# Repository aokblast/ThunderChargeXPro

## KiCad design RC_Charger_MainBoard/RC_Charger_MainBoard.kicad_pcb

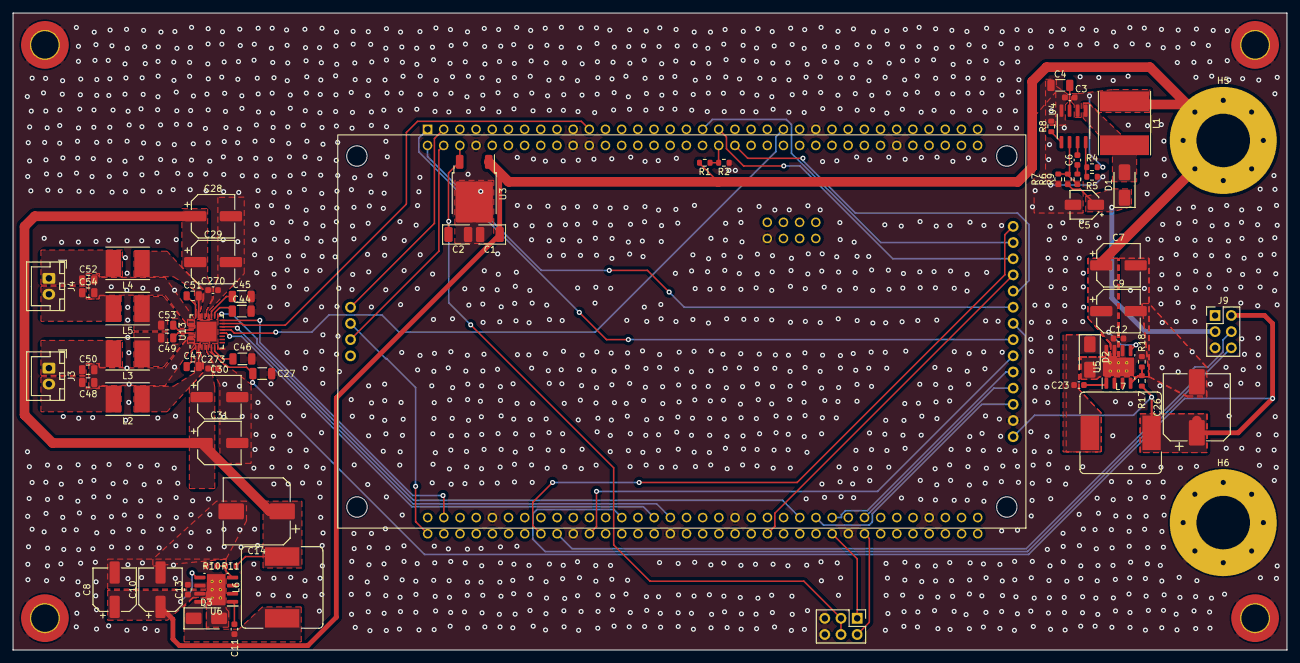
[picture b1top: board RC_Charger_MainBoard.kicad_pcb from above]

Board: 2 copper layers, 200.0 x 100.0 mm, 73 parts (1 on the bottom side), 59 nets.

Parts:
C1, C2: 10u; CP_EIA-3528-21_Kemet-B
C3, C11, C12, C13, C23, C270, C273: 0.1u; C_0603_1608Metric
C4, C27, C44, C45, C46: 1u; C_1206_3216Metric
C5: 10u; CP_Elec_4x5.7
C6: 2.2n; C_0603_1608Metric
C7, C8, C9, C10: 68u; CP_Elec_6.3x7.7
C14, C26: 560u; CP_Elec_10x10
C28, C29, C30, C31: 22u; CP_Elec_6.3x5.4
C47, C49, C51, C53: 0.47u; C_0805_2012Metric
C48, C50, C52, C54: 0.68u; C_0805_2012Metric
D1: CDBA360-HF; D_SMA
D2, D3: SS54F; D_SMA
H1, H2, H3, H4: M4; MountingHole_4.3mm_M4_DIN965_Pad_TopBottom
H5, H6: M8; MountingHole_8.4mm_M8_Pad_Via
J1, J9: Conn_02x03_Odd_Even; PinHeader_2x03_P2.54mm_Vertical
J3: SPK1; JST_XH_B2B-XH-A_1x02_P2.50mm_Vertical
J4: SPK2; JST_XH_B2B-XH-A_1x02_P2.50mm_Vertical
L1: 100u; L_Taiyo-Yuden_NR-80xx_HandSoldering
L2, L3, L4, L5: 10u; L_Taiyo-Yuden_NR-50xx_HandSoldering
L6, L7: 15u; L_Bourns_SRR1260
R1: 68k; R_0603_1608Metric
R2, R10, R17: 10k; R_0603_1608Metric
R4: 53.6k; R_0603_1608Metric
R5: 12.1k; R_0603_1608Metric
R6: 54.9k; R_0603_1608Metric
R7: 2.43k; R_0603_1608Metric
R8: 52.3k; R_0603_1608Metric
R9: 73.2k; R_0603_1608Metric
R11: 3.24k; R_0603_1608Metric
R18: 5.9k; R_0603_1608Metric
U1: NUCLEO-H745ZI-Q; MODULE_NUCLEO-H745ZI-Q
U2: 4-inch SPI screen
U3: L7805; TO-252-2
U4: LM5001MA; SOIC-8_3.9x4.9mm_P1.27mm
U5, U6: TPS5430DDA; Texas_R-PDSO-G8_EP2.95x4.9mm_Mask2.4x3.1mm_ThermalVias
U13: TAS5825MRHB; VQFN-32-1EP_5x5mm_P0.5mm_EP3.1x3.1mm

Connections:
+5V: C2.1, J1.3, J1.4, U1.CN11_6 (5V_EXT), U3.3 (OUT)
/3V3 Buck/FB: R17.1, R18.2, U5.4 (VSENSE)
/5V Buck/FB: R10.1, R11.2, U6.4 (VSENSE)
/5V Buck/VOUT: C14.1, C28.1, C29.1, C30.1, C31.1, C270.1, C273.1, L6.2, R10.2, U13.3 (PVDD), U13.4 (PVDD), U13.21 (PVDD), U13.22 (PVDD)
GND: C1.2, C2.2, C3.2, C4.2, C5.2, C7.2, C8.2, C9.2, C10.2, C12.2, C13.2, C14.2, C26.2, C27.2, C28.2, C29.2, C30.2, C31.2, C44.2, C45.2, C46.2, C48.2, C50.2, C52.2, C54.2, C270.2, C273.2, D2.2 (A), D3.2 (A), H1.1, H2.1, H3.1, H4.1, H6.1, J1.5, J1.6, J9.5, R2.2, R5.1, R7.1, R8.1, R11.1, R18.1, U1.CN6_7 (GND_CN6), U1.CN11_8 (GND), U1.CN11_19 (GND), U1.CN11_20 (GND), U1.CN11_22 (GND), U1.CN11_49 (GND), U1.CN11_60 (GND), U1.CN12_9 (GND), U1.CN12_20 (GND), U1.CN12_32 (AGND), U1.CN12_39 (GND), U1.CN12_54 (GND), U1.CN12_63 (GND), U2.2 (GND), U3.2 (GND), U4.4 (GND), U5.6 (GND), U5.9 (GNDPAD), U6.6 (GND), U6.9 (GNDPAD), U13.5 (DGND), U13.8 (ADR), U13.20 (AGND), U13.25 (PGND), U13.26 (PGND), U13.31 (PGND), U13.32 (PGND), U13.33 (EP)
I2S_CLK: U1.CN12_31 (PB3), U13.14 (SDIN)
I2S_LRCLK: U1.CN12_29 (PB5/PA4), U13.12 (LRCLK)
I2S_MUTE: U1.CN12_47 (PE10), U13.17 (~PDN)
I2S_SCL: U1.CN12_3 (PB8), U13.16 (SCL)
I2S_SDA: U1.CN11_21 (PB7), U13.15 (SDA)
I2S_SDO: U1.CN11_45 (PD7), U13.13 (SCLK)
IO_SCL: J9.6, U1.CN12_25 (PB10)
IO_SDA: J9.4, U1.CN12_18 (PB11)
unnamed: C6.2, R9.2
unnamed: D1.2 (A), L1.2, U4.1 (SW)
unnamed: C23.2, D2.1 (K), L7.1, U5.8 (PH)
unnamed: C11.2, D3.1 (K), L6.1, U6.8 (PH)
unnamed: C50.1, J3.1, L3.2
unnamed: C48.1, J3.2, L2.2
unnamed: C52.1, J4.1, L4.2
unnamed: C54.1, J4.2, L5.2
unnamed: C6.1, U4.7 (COMP)
unnamed: R4.1, R5.2, U4.8 (EN)
unnamed: R6.1, R7.2, R9.1, U4.6 (FB)
unnamed: R8.2, U4.5 (RT)
unnamed: C4.1, U4.3 (VCC)
unnamed: C23.1, U5.1 (BOOT)
unnamed: C11.1, U6.1 (BOOT)
unnamed: C45.1, U13.19 (AVDD)
unnamed: C47.1, U13.1 (BST_A+)
unnamed: C49.1, U13.29 (BST_A-)
unnamed: C51.1, U13.24 (BST_B+)
unnamed: C53.1, U13.28 (BST_B-)
unnamed: C44.1, U13.18 (GVDD)
unnamed: C47.2, L2.1, U13.2 (OUT_A+)
unnamed: C49.2, L3.1, U13.30 (OUT_A-)
unnamed: C51.2, L4.1, U13.23 (OUT_B+)
unnamed: C53.2, L5.1, U13.27 (OUT_B-)
unnamed: C46.1, U13.7 (VR_DIG)
SDMMC1_CK: U1.CN11_3 (PC12), U2.18 (SD_SCK)
SDMMC1_CMD: U1.CN11_4 (PD2), U2.16 (SD_MOSI)
SDMMC1_DO: U1.CN12_2 (PC8), U2.17 (SD_MISO)
SERVO1: J1.1, U1.CN12_52 (PE9)
SERVO2: J1.2, U1.CN12_56 (PE11)
SSPI_MISO: U1.CN11_2 (PC11), U2.9 (SDO(MISO))
SSPI_MOSI: U1.CN12_22 (PB2), U2.6 (SDI(MOSI))
SSPI_SCK: U1.CN11_1 (PC10), U2.7 (SCK)
S_CS: U1.CN12_49 (PE12), U2.3 (CS)
S_DCRS: U1.CN12_51 (PE14), U2.5 (DC/RS)
S_PWR: C26.1, C27.1, J9.2, L7.2, R17.2, U2.1 (VCC), U2.8 (LED), U13.6 (DVDD)
S_RST: U1.CN12_55 (PE13), U2.4 (RESET)
TSPI_MISO: U1.CN11_35 (PC2), U2.13 (T_DO)
TSPI_MOSI: U1.CN11_37 (PC3), U2.12 (T_DIN)
TSPI_SCK: U1.CN11_40 (PD3), U2.10 (T_CLK)
T_CS: U1.CN12_44 (PE7), U2.11 (T_CS)
T_IRQ: U1.CN12_16 (PB12), U2.14 (T_IRQ)
VCC: C5.1, D1.1 (K), J9.3, R6.2
VIN: C1.1, C3.1, C7.1, C8.1, C9.1, C10.1, C12.1, C13.1, H5.1, L1.1, R1.1, R4.2, U3.1 (IN), U4.2 (VIN), U5.5 (EN), U5.7 (VIN), U6.5 (EN), U6.7 (VIN)
VSENSE: R1.2, R2.1, U1.CN11_38 (PC0)

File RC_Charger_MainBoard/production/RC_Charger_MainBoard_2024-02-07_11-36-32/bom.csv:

Designator,Footprint,Quantity,Value,LCSC Part #
"C1, C2",CP_EIA-3528-21_Kemet-B,2,10u,
"C10, C7, C8, C9",CP_Elec_6.3x7.7,4,68u,
"C11, C12, C13, C23, C270, C273, C3",0603,7,0.1u,
"C14, C26",CP_Elec_10x10,2,560u,
"C27, C4, C44, C45, C46",1206,5,1u,
"C28, C29, C30, C31",CP_Elec_6.3x5.4,4,22u,
"C47, C49, C51, C53",0805,4,0.47u,
"C48, C50, C52, C54",0805,4,0.68u,
C5,CP_Elec_4x5.7,1,10u,
C6,0603,1,2.2n,
D1,D_SMA,1,CDBA360-HF,
"D2, D3",D_SMA,2,SS54F,
"H1, H2, H3, H4",MountingHole_4.3mm_M4_DIN965_Pad_TopBottom,4,M4,
"H5, H6",MountingHole_8.4mm_M8_Pad_Via,2,M8,
"J1, J9",PinHeader_2x03_P2.54mm_Vertical,2,Conn_02x03_Odd_Even,
J3,JST_XH_B2B-XH-A_1x02_P2.50mm_Vertical,1,SPK1,
J4,JST_XH_B2B-XH-A_1x02_P2.50mm_Vertical,1,SPK2,
L1,L_Taiyo-Yuden_NR-80xx_HandSoldering,1,100u,
"L2, L3, L4, L5",L_Taiyo-Yuden_NR-50xx_HandSoldering,4,10u,
"L6, L7",L_Bourns_SRR1260,2,15u,
R1,0603,1,68k,
"R10, R17, R2",0603,3,10k,
R11,0603,1,3.24k,
R18,0603,1,5.9k,
R4,0603,1,53.6k,
R5,0603,1,12.1k,
R6,0603,1,54.9k,
R7,0603,1,2.43k,
R8,0603,1,52.3k,
R9,0603,1,73.2k,
U1,MODULE_NUCLEO-H745ZI-Q,1,NUCLEO-H745ZI-Q,
U13,VQFN-32-1EP_5x5mm_P0.5mm_EP3.1x3.1mm,1,TAS5825MRHB,
U2,4-inch SPI screen,1,~,
U3,TO-252-2,1,L7805,
U4,SOIC-8_3.9x4.9mm_P1.27mm,1,LM5001MA,
"U5, U6",Texas_R-PDSO-G8_EP2.95x4.9mm_Mask2.4x3.1mm_ThermalVias,2,TPS5430DDA,

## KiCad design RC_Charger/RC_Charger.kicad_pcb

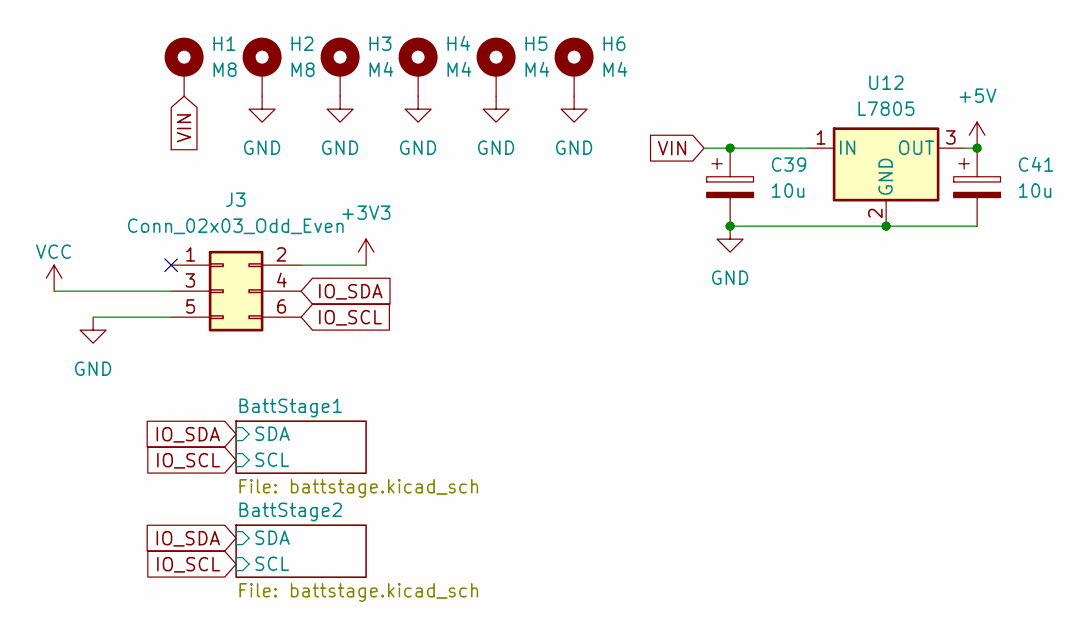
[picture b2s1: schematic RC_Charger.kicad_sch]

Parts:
C39, C41: 10u; CP_EIA-3528-21_Kemet-B
H1, H2: M8; MountingHole_8.4mm_M8_Pad_Via
H3, H4, H5, H6: M4; MountingHole_4.3mm_M4_DIN965_Pad_TopBottom
J3: Conn_02x03_Odd_Even; PinHeader_2x03_P2.54mm_Vertical
U12: L7805; TO-252-2

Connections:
+3V3: J3.2; also elsewhere on the board
+5V: C41.1, U12.3 (OUT); also elsewhere on the board
GND: C39.2, C41.2, H2.1, H3.1, H4.1, H5.1, H6.1, J3.5, U12.2 (GND); also elsewhere on the board
IO_SCL: J3.6; also elsewhere on the board
IO_SDA: J3.4; also elsewhere on the board
VCC: J3.3; also elsewhere on the board
VIN: C39.1, H1.1, U12.1 (IN); also elsewhere on the board

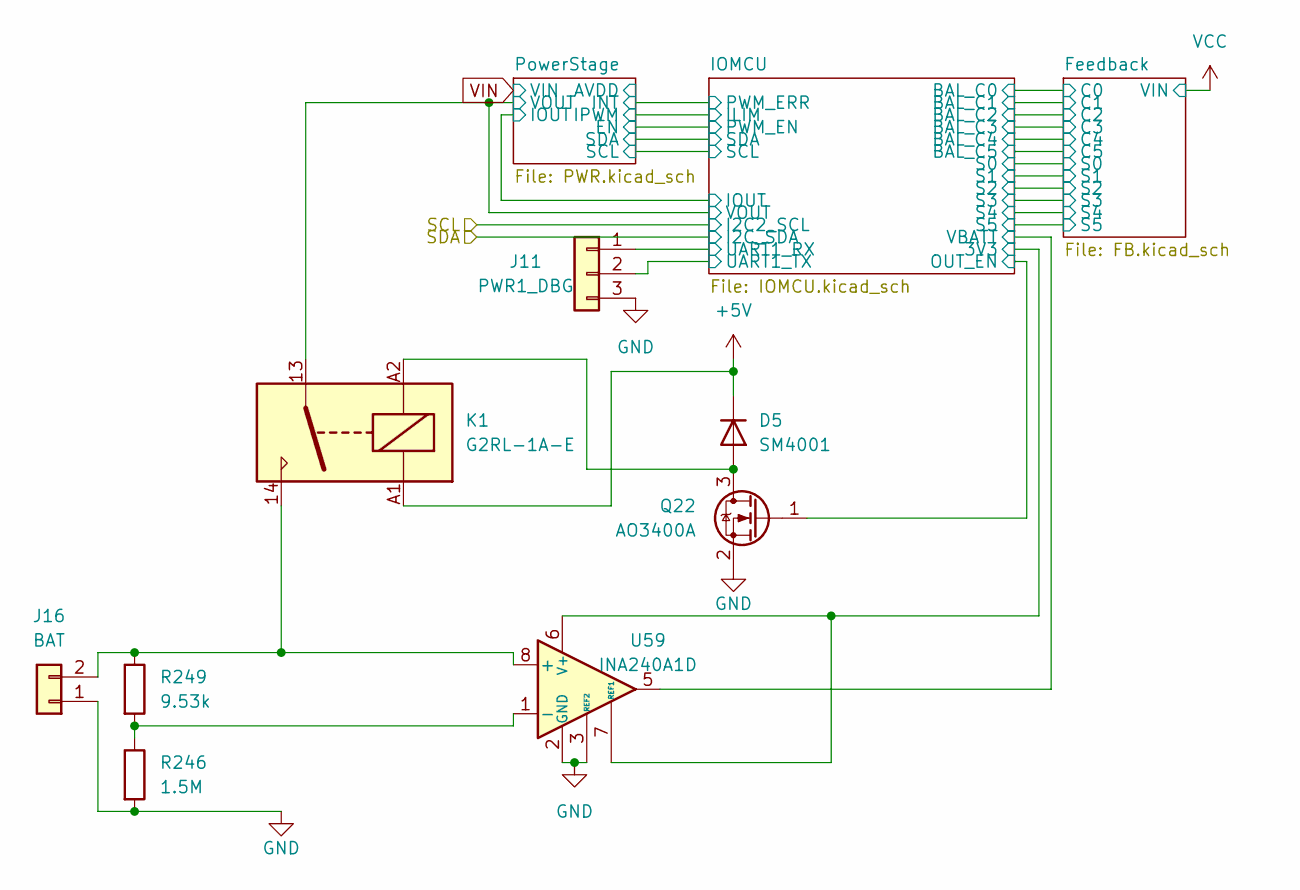
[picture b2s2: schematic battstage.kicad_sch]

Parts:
D5: SM4001; D_MELF
J11: PWR1_DBG; PinHeader_1x03_P2.54mm_Vertical
J16: BAT; TerminalBlock_Dinkle_DT-55-B01X-02_P10.00mm
K1: G2RL-1A-E; Relay_SPST_Omron_G2RL-1A-E
Q22: AO3400A; SOT-23
R246: 1.5M; R_0603_1608Metric
R249: 9.53k; R_0603_1608Metric
U59: INA240A1D; SOIC-8_3.9x4.9mm_P1.27mm

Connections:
+3V3: U59.6 (V+), U59.7 (REF1); also elsewhere on the board
+5V: D5.1 (K), K1.A1; also elsewhere on the board
/BattStage1/IOMCU/UART1_RX: J11.1; also elsewhere on the board
/BattStage1/IOMCU/UART1_TX: J11.2; also elsewhere on the board
/BattStage1/PowerStage/VOUT: K1.13; also elsewhere on the board
/BattStage2/IOMCU/OUT_EN: Q22.1 (G); also elsewhere on the board
/BattStage2/IOMCU/VBATT: U59.5; also elsewhere on the board
GND: J11.3, J16.1, Q22.2 (S), R246.2, U59.2 (GND), U59.3 (REF2), U59.4 (GND); also elsewhere on the board
unnamed: R246.1, R249.2, U59.1 (-)

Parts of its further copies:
D6: SM4001; D_MELF
J5: PWR1_DBG; PinHeader_1x03_P2.54mm_Vertical
J19: BAT; TerminalBlock_Dinkle_DT-55-B01X-02_P10.00mm
K2: G2RL-1A-E; Relay_SPST_Omron_G2RL-1A-E
Q21: AO3400A; SOT-23
R245: 1.5M; R_0603_1608Metric
R252: 9.53k; R_0603_1608Metric
U62: INA240A1D; SOIC-8_3.9x4.9mm_P1.27mm

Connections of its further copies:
+3V3: U62.6 (V+), U62.7 (REF1); also elsewhere on the board
+5V: D6.1 (K), K2.A1; also elsewhere on the board
/BattStage1/IOMCU/OUT_EN: Q21.1 (G); also elsewhere on the board
/BattStage1/IOMCU/VBATT: U62.5; also elsewhere on the board
/BattStage2/IOMCU/UART1_RX: J5.1; also elsewhere on the board
/BattStage2/IOMCU/UART1_TX: J5.2; also elsewhere on the board
/BattStage2/PowerStage/VOUT: K2.13; also elsewhere on the board
GND: J5.3, J19.1, Q21.2 (S), R245.2, U62.2 (GND), U62.3 (REF2), U62.4 (GND); also elsewhere on the board
unnamed: R245.1, R252.2, U62.1 (-)

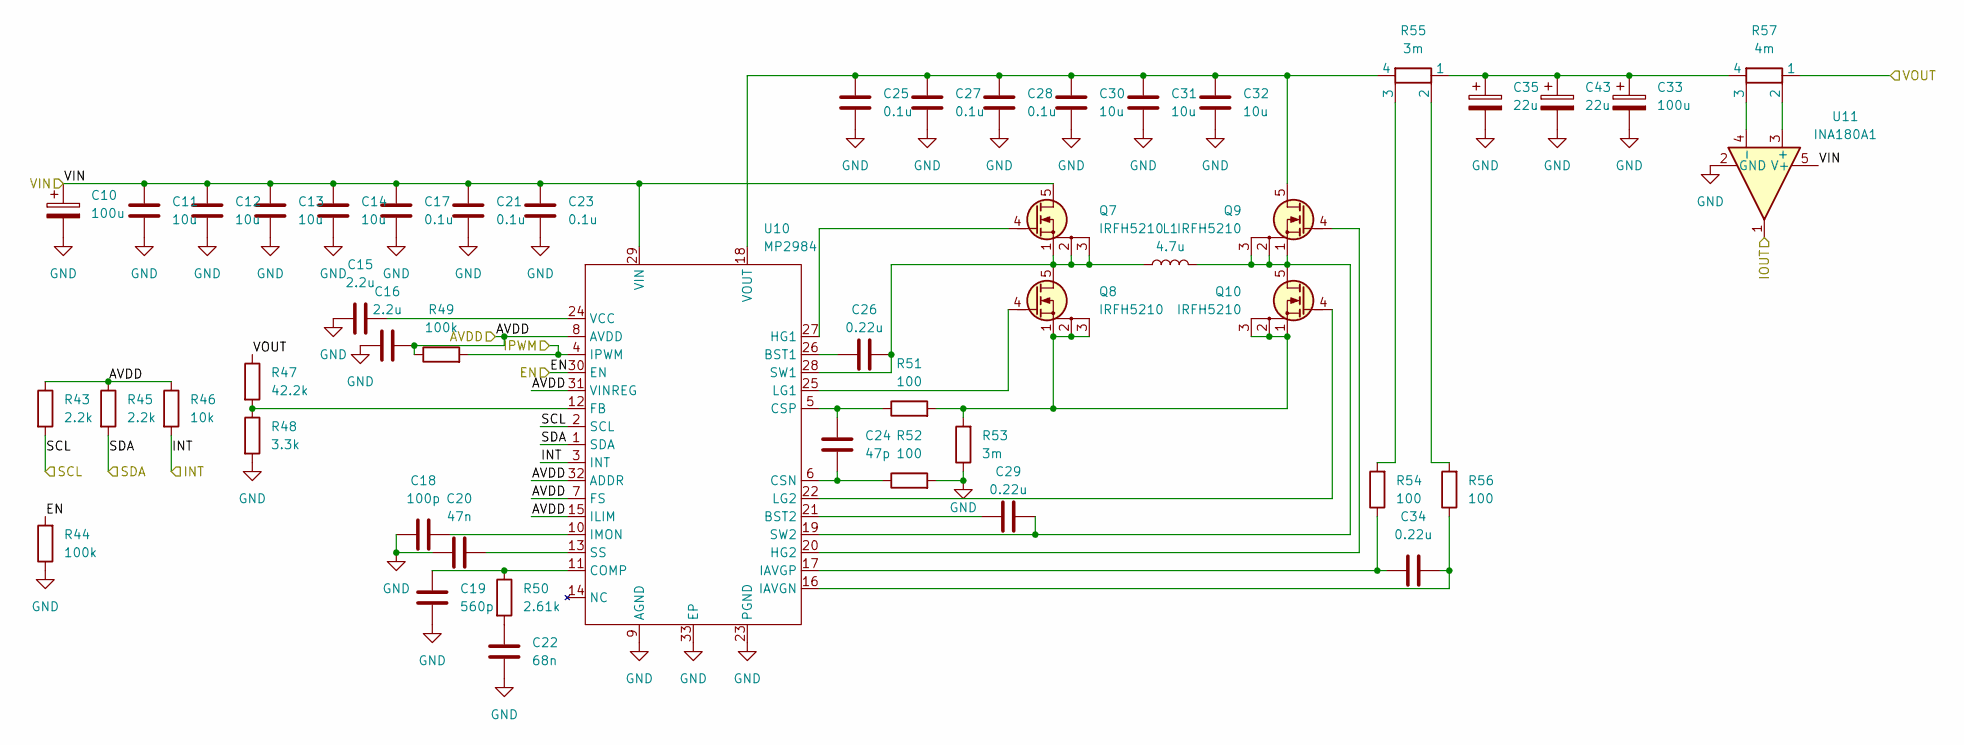
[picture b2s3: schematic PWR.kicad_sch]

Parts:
C10, C33: 100u; CP_Elec_6.3x7.7
C11, C12, C13, C14, C30, C31, C32: 10u; C_1206_3216Metric
C15, C16: 2.2u; C_0805_2012Metric
C17, C21, C23, C25, C27, C28: 0.1u; C_0603_1608Metric
C18: 100p; C_0603_1608Metric
C19: 560p; C_0603_1608Metric
C20: 47n; C_0603_1608Metric
C22: 68n; C_0603_1608Metric
C24: 47p; C_0603_1608Metric
C26, C29, C34: 0.22u; C_0603_1608Metric
C35, C43: 22u; CP_Elec_6.3x5.4
L1: 4.7u; L_Bourns_SRP1770TA_16.9x16.9mm
Q7, Q8, Q9, Q10: IRFH5210; PQFN-8-EP_6x5mm_P1.27mm_Generic
R43, R45: 2.2k; R_0603_1608Metric
R44, R49: 100k; R_0603_1608Metric
R46: 10k; R_0603_1608Metric
R47: 42.2k; R_0603_1608Metric
R48: 3.3k; R_0603_1608Metric
R50: 2.61k; R_0603_1608Metric
R51, R52, R54, R56: 100; R_0603_1608Metric
R53: 3m; R_Shunt_1575
R55: 3m; R_Shunt_Vishay_WSK2512_6332Metric_T2.21mm
R57: 4m; R_Shunt_Vishay_WSK2512_6332Metric_T2.21mm
U10: MP2984; QFN-32-1EP_4x4mm_P0.4mm_EP2.65x2.65mm
U11: INA180A1; SOT-23-5

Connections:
/BattStage1/IOMCU/ILIM: R49.2, U10.4 (IPWM); also elsewhere on the board
/BattStage1/IOMCU/IOUT: U11.1; also elsewhere on the board
/BattStage1/PowerStage/AVDD: C16.2, R43.1, R45.1, R46.1, R49.1, U10.7 (FS), U10.8 (AVDD), U10.15 (ILIM), U10.31 (VINREG), U10.32 (ADDR)
/BattStage1/PowerStage/EN: R44.2, U10.30 (EN); also elsewhere on the board
/BattStage1/PowerStage/INT: R46.2, U10.3 (INT); also elsewhere on the board
/BattStage1/PowerStage/SCL: R43.2, U10.2 (SCL); also elsewhere on the board
/BattStage1/PowerStage/SDA: R45.2, U10.1 (SDA); also elsewhere on the board
/BattStage1/PowerStage/VOUT: R47.1, R57.1; also elsewhere on the board
GND: C10.2, C11.2, C12.2, C13.2, C14.2, C15.1, C16.1, C17.2, C18.1, C19.2, C20.2, C21.2, C22.2, C23.2, C25.2, C27.2, C28.2, C30.2, C31.2, C32.2, C33.2, C35.2, C43.2, R44.1, R48.2, R52.2, R53.1, U10.9 (AGND), U10.23 (PGND), U10.33 (EP), U11.2 (GND); also elsewhere on the board
unnamed: C22.1, R50.2
unnamed: C33.1, C35.1, C43.1, R55.1, R57.4
unnamed: Q7.4 (G), U10.27 (HG1)
unnamed: C26.2, L1.1, Q7.1 (S), Q7.2 (S), Q7.3 (S), Q8.5 (D), U10.28 (SW1)
unnamed: Q8.4 (G), U10.25 (LG1)
unnamed: C25.1, C27.1, C28.1, C30.1, C31.1, C32.1, Q9.5 (D), R55.4, U10.18 (VOUT)
unnamed: Q9.4 (G), U10.20 (HG2)
unnamed: C29.2, L1.2, Q9.1 (S), Q9.2 (S), Q9.3 (S), Q10.5 (D), U10.19 (SW2)
unnamed: Q10.4 (G), U10.22 (LG2)
unnamed: Q8.1 (S), Q8.2 (S), Q8.3 (S), Q10.1 (S), Q10.2 (S), Q10.3 (S), R51.2, R53.2
unnamed: R54.2, R55.3
unnamed: R55.2, R56.2
unnamed: C26.1, U10.26 (BST1)
unnamed: C29.1, U10.21 (BST2)
unnamed: C19.1, R50.1, U10.11 (COMP)
unnamed: C24.2, R52.1, U10.6 (CSN)
unnamed: C24.1, R51.1, U10.5 (CSP)
unnamed: R47.2, R48.1, U10.12 (FB)
unnamed: C34.2, R56.1, U10.16 (IAVGN)
unnamed: C34.1, R54.1, U10.17 (IAVGP)
unnamed: C18.2, U10.10 (IMON)
unnamed: C20.1, U10.13 (SS)
unnamed: C15.2, U10.24 (VCC)
unnamed: R57.2, U11.3 (+)
unnamed: R57.3, U11.4 (-)
VIN: C10.1, C11.1, C12.1, C13.1, C14.1, C17.1, C21.1, C23.1, Q7.5 (D), U10.29 (VIN), U11.5 (V+); also elsewhere on the board

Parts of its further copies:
C36, C44: 22u; CP_Elec_6.3x5.4
C42, C55: 100u; CP_Elec_6.3x7.7
C56, C57, C58, C59, C75, C76, C77: 10u; C_1206_3216Metric
C60, C61: 2.2u; C_0805_2012Metric
C62, C66, C68, C70, C72, C73: 0.1u; C_0603_1608Metric
C63: 100p; C_0603_1608Metric
C64: 560p; C_0603_1608Metric
C65: 47n; C_0603_1608Metric
C67: 68n; C_0603_1608Metric
C69: 47p; C_0603_1608Metric
C71, C74, C79: 0.22u; C_0603_1608Metric
L6: 4.7u; L_Bourns_SRP1770TA_16.9x16.9mm
Q11, Q12, Q13, Q14: IRFH5210; PQFN-8-EP_6x5mm_P1.27mm_Generic
R62, R64: 2.2k; R_0603_1608Metric
R63, R68: 100k; R_0603_1608Metric
R65: 10k; R_0603_1608Metric
R66: 42.2k; R_0603_1608Metric
R67: 3.3k; R_0603_1608Metric
R69: 2.61k; R_0603_1608Metric
R70, R71, R73, R75: 100; R_0603_1608Metric
R72: 3m; R_Shunt_1575
R74: 3m; R_Shunt_Vishay_WSK2512_6332Metric_T2.21mm
R76: 4m; R_Shunt_Vishay_WSK2512_6332Metric_T2.21mm
U16: MP2984; QFN-32-1EP_4x4mm_P0.4mm_EP2.65x2.65mm
U17: INA180A1; SOT-23-5

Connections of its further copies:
/BattStage2/IOMCU/ILIM: R68.2, U16.4 (IPWM); also elsewhere on the board
/BattStage2/IOMCU/IOUT: U17.1; also elsewhere on the board
/BattStage2/PowerStage/AVDD: C61.2, R62.1, R64.1, R65.1, R68.1, U16.7 (FS), U16.8 (AVDD), U16.15 (ILIM), U16.31 (VINREG), U16.32 (ADDR)
/BattStage2/PowerStage/EN: R63.2, U16.30 (EN); also elsewhere on the board
/BattStage2/PowerStage/INT: R65.2, U16.3 (INT); also elsewhere on the board
/BattStage2/PowerStage/SCL: R62.2, U16.2 (SCL); also elsewhere on the board
/BattStage2/PowerStage/SDA: R64.2, U16.1 (SDA); also elsewhere on the board
/BattStage2/PowerStage/VOUT: R66.1, R76.1; also elsewhere on the board
GND: C36.2, C42.2, C44.2, C55.2, C56.2, C57.2, C58.2, C59.2, C60.1, C61.1, C62.2, C63.1, C64.2, C65.2, C66.2, C67.2, C68.2, C70.2, C72.2, C73.2, C75.2, C76.2, C77.2, R63.1, R67.2, R71.2, R72.1, U16.9 (AGND), U16.23 (PGND), U16.33 (EP), U17.2 (GND); also elsewhere on the board
unnamed: C36.1, C42.1, C44.1, R74.1, R76.4
unnamed: C67.1, R69.2
unnamed: Q11.4 (G), U16.27 (HG1)
unnamed: C71.2, L6.1, Q11.1 (S), Q11.2 (S), Q11.3 (S), Q12.5 (D), U16.28 (SW1)
unnamed: Q12.4 (G), U16.25 (LG1)
unnamed: Q12.1 (S), Q12.2 (S), Q12.3 (S), Q14.1 (S), Q14.2 (S), Q14.3 (S), R70.2, R72.2
unnamed: C70.1, C72.1, C73.1, C75.1, C76.1, C77.1, Q13.5 (D), R74.4, U16.18 (VOUT)
unnamed: Q13.4 (G), U16.20 (HG2)
unnamed: C74.2, L6.2, Q13.1 (S), Q13.2 (S), Q13.3 (S), Q14.5 (D), U16.19 (SW2)
unnamed: Q14.4 (G), U16.22 (LG2)
unnamed: R73.2, R74.3
unnamed: R74.2, R75.2
unnamed: C71.1, U16.26 (BST1)
unnamed: C74.1, U16.21 (BST2)
unnamed: C64.1, R69.1, U16.11 (COMP)
unnamed: C69.2, R71.1, U16.6 (CSN)
unnamed: C69.1, R70.1, U16.5 (CSP)
unnamed: R66.2, R67.1, U16.12 (FB)
unnamed: C79.2, R75.1, U16.16 (IAVGN)
unnamed: C79.1, R73.1, U16.17 (IAVGP)
unnamed: C63.2, U16.10 (IMON)
unnamed: C65.1, U16.13 (SS)
unnamed: C60.2, U16.24 (VCC)
unnamed: R76.2, U17.3 (+)
unnamed: R76.3, U17.4 (-)
VIN: C55.1, C56.1, C57.1, C58.1, C59.1, C62.1, C66.1, C68.1, Q11.5 (D), U16.29 (VIN), U17.5 (V+); also elsewhere on the board

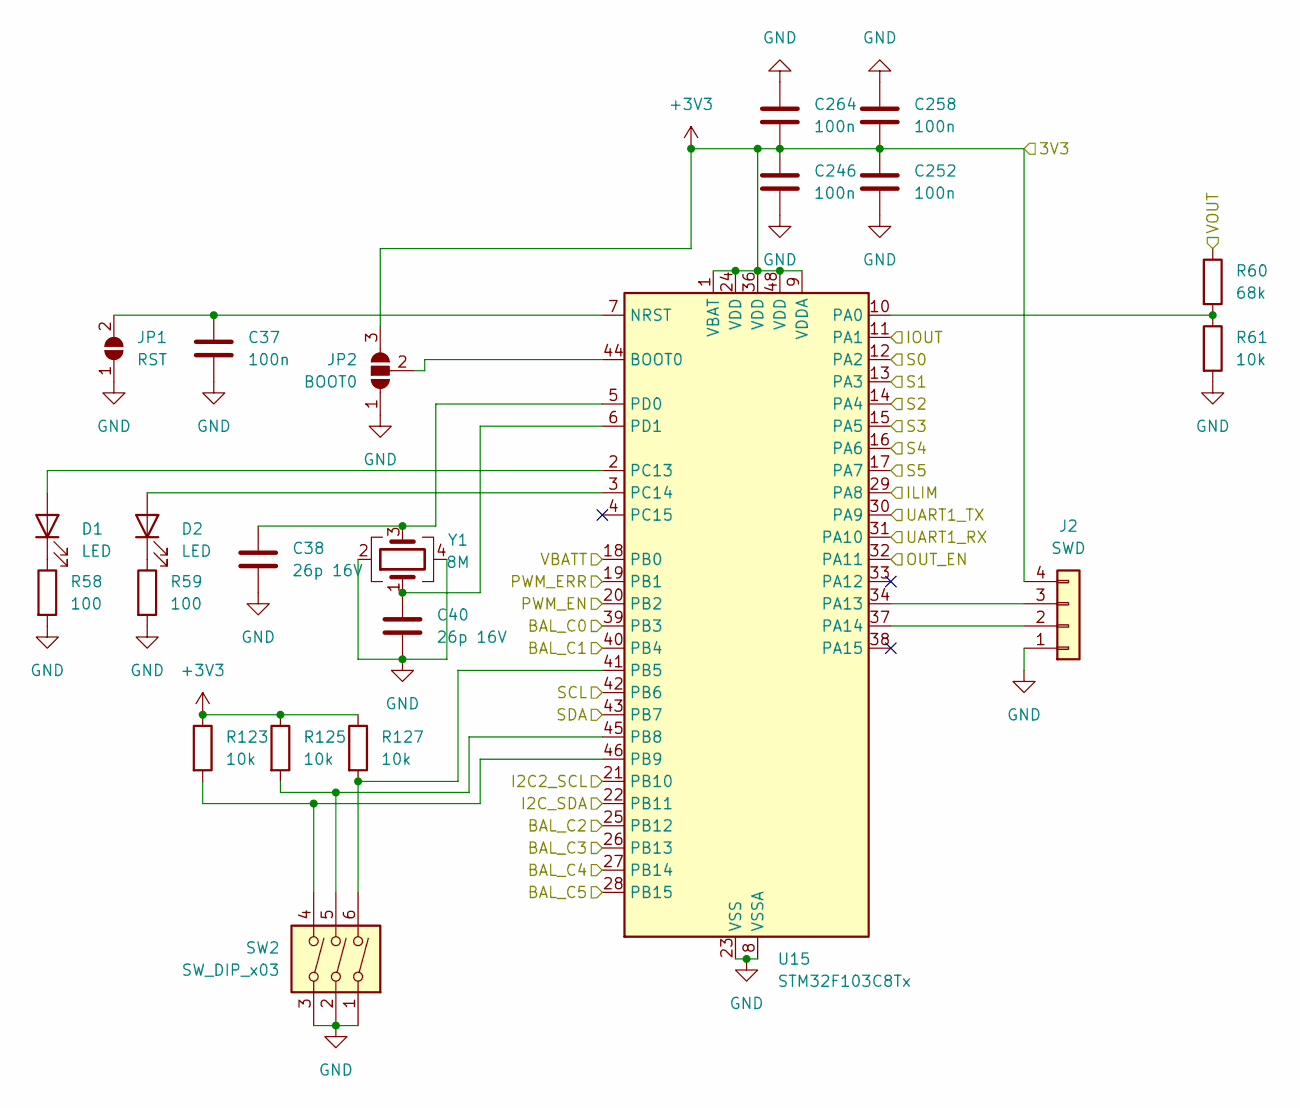
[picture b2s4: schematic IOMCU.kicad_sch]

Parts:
C37, C246, C252, C258, C264: 100n; C_0603_1608Metric
C38, C40: 26p 16V; C_0603_1608Metric
D1, D2: LED; LED_0603_1608Metric
J2: SWD; PinHeader_1x04_P2.54mm_Vertical
JP1: RST; SolderJumper-2_P1.3mm_Open_RoundedPad1.0x1.5mm
JP2: BOOT0; SolderJumper-3_P1.3mm_Open_Pad1.0x1.5mm
R58, R59: 100; R_0603_1608Metric
R60: 68k; R_0603_1608Metric
R61, R123, R125, R127: 10k; R_0603_1608Metric
SW2: SW_DIP_x03; SW_DIP_SPSTx03_Slide_9.78x9.8mm_W8.61mm_P2.54mm
U15: STM32F103C8Tx; LQFP-48_7x7mm_P0.5mm
Y1: 8M; Crystal_SMD_Abracon_ABM3B-4Pin_5.0x3.2mm

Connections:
+3V3: C246.1, C252.1, C258.2, C264.2, J2.4, JP2.3 (B), R123.1, R125.1, R127.1, U15.1 (VBAT), U15.9 (VDDA), U15.24 (VDD), U15.36 (VDD), U15.48 (VDD); also elsewhere on the board
/BattStage1/Feedback/C0: U15.39 (PB3); also elsewhere on the board
/BattStage1/Feedback/C1: U15.40 (PB4); also elsewhere on the board
/BattStage1/Feedback/C2: U15.25 (PB12); also elsewhere on the board
/BattStage1/Feedback/C3: U15.26 (PB13); also elsewhere on the board
/BattStage1/Feedback/C4: U15.27 (PB14); also elsewhere on the board
/BattStage1/Feedback/C5: U15.28 (PB15); also elsewhere on the board
/BattStage1/Feedback/S0: U15.12 (PA2); also elsewhere on the board
/BattStage1/Feedback/S1: U15.13 (PA3); also elsewhere on the board
/BattStage1/Feedback/S2: U15.14 (PA4); also elsewhere on the board
/BattStage1/Feedback/S3: U15.15 (PA5); also elsewhere on the board
/BattStage1/Feedback/S4: U15.16 (PA6); also elsewhere on the board
/BattStage1/Feedback/S5: U15.17 (PA7); also elsewhere on the board
/BattStage1/IOMCU/ILIM: U15.29 (PA8); also elsewhere on the board
/BattStage1/IOMCU/IOUT: U15.11 (PA1); also elsewhere on the board
/BattStage1/IOMCU/OUT_EN: U15.32 (PA11); also elsewhere on the board
/BattStage1/IOMCU/UART1_RX: U15.31 (PA10); also elsewhere on the board
/BattStage1/IOMCU/UART1_TX: U15.30 (PA9); also elsewhere on the board
/BattStage1/IOMCU/VBATT: U15.18 (PB0); also elsewhere on the board
/BattStage1/PowerStage/EN: U15.20 (PB2); also elsewhere on the board
/BattStage1/PowerStage/INT: U15.19 (PB1); also elsewhere on the board
/BattStage1/PowerStage/SCL: U15.42 (PB6); also elsewhere on the board
/BattStage1/PowerStage/SDA: U15.43 (PB7); also elsewhere on the board
/BattStage1/PowerStage/VOUT: R60.1; also elsewhere on the board
GND: C37.2, C38.1, C40.1, C246.2, C252.2, C258.1, C264.1, J2.1, JP1.1 (A), JP2.1 (A), R58.2, R59.2, R61.2, SW2.1, SW2.2, SW2.3, U15.8 (VSSA), U15.23 (VSS), U15.35 (VSS), U15.47 (VSS), Y1.2, Y1.4; also elsewhere on the board
IO_SCL: U15.21 (PB10); also elsewhere on the board
IO_SDA: U15.22 (PB11); also elsewhere on the board
unnamed: D1.2 (A), U15.2 (PC13)
unnamed: D1.1 (K), R58.1
unnamed: D2.2 (A), U15.3 (PC14)
unnamed: D2.1 (K), R59.1
unnamed: J2.2, U15.37 (PA14)
unnamed: J2.3, U15.34 (PA13)
unnamed: C37.1, JP1.2 (B), U15.7 (NRST)
unnamed: JP2.2 (C), U15.44 (BOOT0)
unnamed: R60.2, R61.1, U15.10 (PA0)
unnamed: C38.2, U15.5 (PD0), Y1.3
unnamed: C40.2, U15.6 (PD1), Y1.1

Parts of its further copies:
C91, C247, C253, C259, C265: 100n; C_0603_1608Metric
C92, C94: 26p 16V; C_0603_1608Metric
D3, D4: LED; LED_0603_1608Metric
J7: SWD; PinHeader_1x04_P2.54mm_Vertical
JP3: RST; SolderJumper-2_P1.3mm_Open_RoundedPad1.0x1.5mm
JP4: BOOT0; SolderJumper-3_P1.3mm_Open_Pad1.0x1.5mm
R119, R120: 100; R_0603_1608Metric
R121: 68k; R_0603_1608Metric
R122, R124, R126, R128: 10k; R_0603_1608Metric
SW1: SW_DIP_x03; SW_DIP_SPSTx03_Slide_9.78x9.8mm_W8.61mm_P2.54mm
U28: STM32F103C8Tx; LQFP-48_7x7mm_P0.5mm
Y2: 8M; Crystal_SMD_Abracon_ABM3B-4Pin_5.0x3.2mm

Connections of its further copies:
+3V3: C247.1, C253.1, C259.2, C265.2, J7.4, JP4.3 (B), R124.1, R126.1, R128.1, U28.1 (VBAT), U28.9 (VDDA), U28.24 (VDD), U28.36 (VDD), U28.48 (VDD); also elsewhere on the board
/BattStage2/Feedback/C0: U28.39 (PB3); also elsewhere on the board
/BattStage2/Feedback/C1: U28.40 (PB4); also elsewhere on the board
/BattStage2/Feedback/C2: U28.25 (PB12); also elsewhere on the board
/BattStage2/Feedback/C3: U28.26 (PB13); also elsewhere on the board
/BattStage2/Feedback/C4: U28.27 (PB14); also elsewhere on the board
/BattStage2/Feedback/C5: U28.28 (PB15); also elsewhere on the board
/BattStage2/Feedback/S0: U28.12 (PA2); also elsewhere on the board
/BattStage2/Feedback/S1: U28.13 (PA3); also elsewhere on the board
/BattStage2/Feedback/S2: U28.14 (PA4); also elsewhere on the board
/BattStage2/Feedback/S3: U28.15 (PA5); also elsewhere on the board
/BattStage2/Feedback/S4: U28.16 (PA6); also elsewhere on the board
/BattStage2/Feedback/S5: U28.17 (PA7); also elsewhere on the board
/BattStage2/IOMCU/ILIM: U28.29 (PA8); also elsewhere on the board
/BattStage2/IOMCU/IOUT: U28.11 (PA1); also elsewhere on the board
/BattStage2/IOMCU/OUT_EN: U28.32 (PA11); also elsewhere on the board
/BattStage2/IOMCU/UART1_RX: U28.31 (PA10); also elsewhere on the board
/BattStage2/IOMCU/UART1_TX: U28.30 (PA9); also elsewhere on the board
/BattStage2/IOMCU/VBATT: U28.18 (PB0); also elsewhere on the board
/BattStage2/PowerStage/EN: U28.20 (PB2); also elsewhere on the board
/BattStage2/PowerStage/INT: U28.19 (PB1); also elsewhere on the board
/BattStage2/PowerStage/SCL: U28.42 (PB6); also elsewhere on the board
/BattStage2/PowerStage/SDA: U28.43 (PB7); also elsewhere on the board
/BattStage2/PowerStage/VOUT: R121.1; also elsewhere on the board
GND: C91.2, C92.1, C94.1, C247.2, C253.2, C259.1, C265.1, J7.1, JP3.1 (A), JP4.1 (A), R119.2, R120.2, R122.2, SW1.1, SW1.2, SW1.3, U28.8 (VSSA), U28.23 (VSS), U28.35 (VSS), U28.47 (VSS), Y2.2, Y2.4; also elsewhere on the board
IO_SCL: U28.21 (PB10); also elsewhere on the board
IO_SDA: U28.22 (PB11); also elsewhere on the board
unnamed: D3.2 (A), U28.2 (PC13)
unnamed: D3.1 (K), R119.1
unnamed: D4.2 (A), U28.3 (PC14)
unnamed: D4.1 (K), R120.1
unnamed: J7.2, U28.37 (PA14)
unnamed: J7.3, U28.34 (PA13)
unnamed: C91.1, JP3.2 (B), U28.7 (NRST)
unnamed: JP4.2 (C), U28.44 (BOOT0)
unnamed: R121.2, R122.1, U28.10 (PA0)
unnamed: C92.2, U28.5 (PD0), Y2.3
unnamed: C94.2, U28.6 (PD1), Y2.1
